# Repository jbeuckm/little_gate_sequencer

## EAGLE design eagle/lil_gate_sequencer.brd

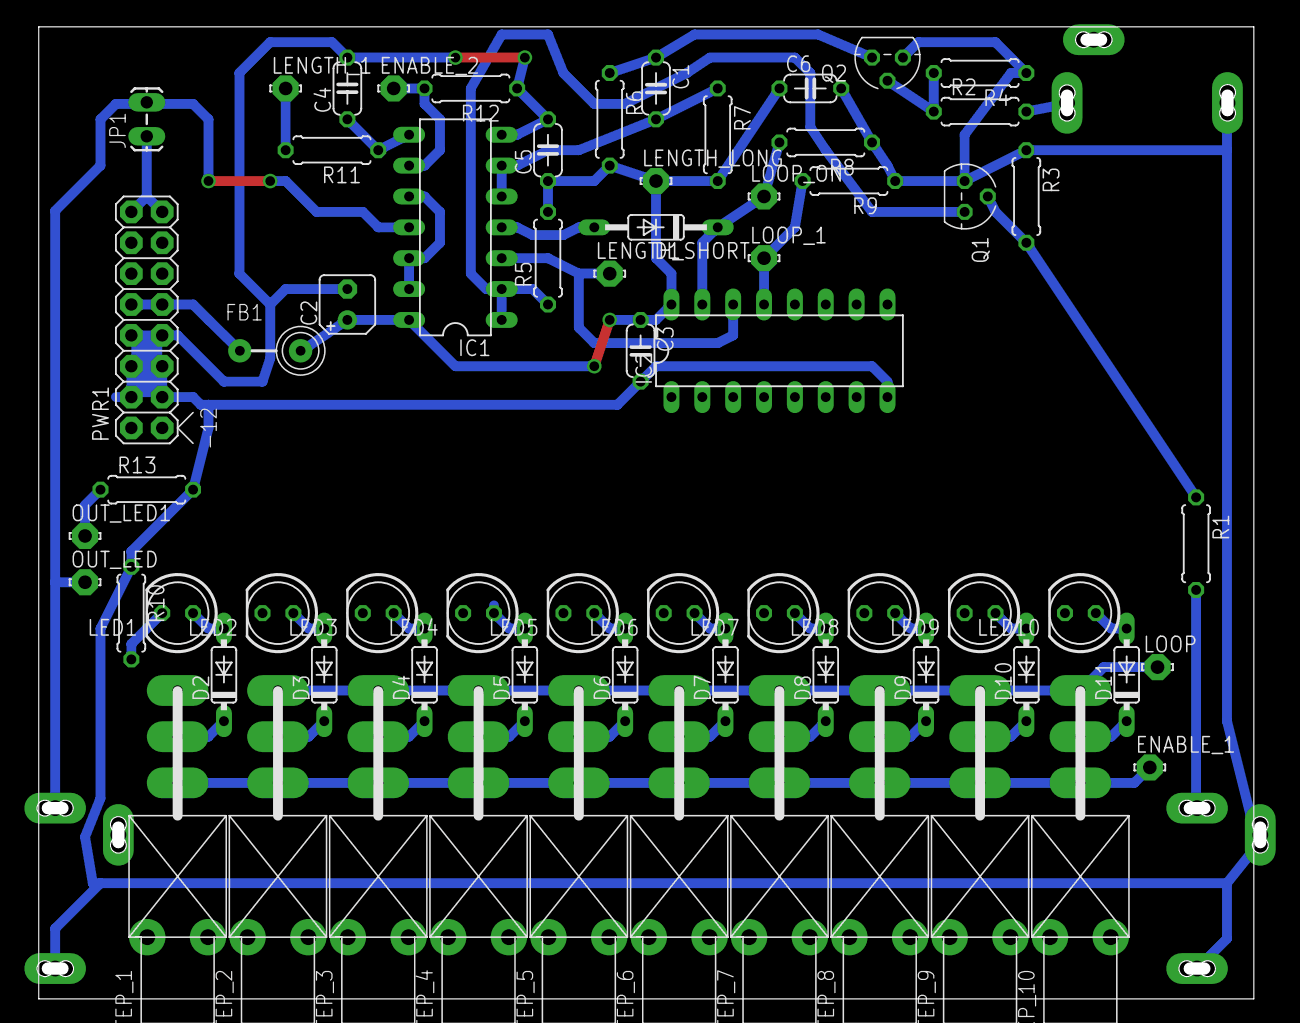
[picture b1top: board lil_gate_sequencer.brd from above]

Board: 2 copper layers, 100.0 x 79.0 mm, 70 parts (0 on the bottom side), 44 nets.

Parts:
C1, C4: 100p; C050-024X044
C2: 10u; B45181A
C3, C5, C6: 100n; C050-024X044
CLK: AUDIO-JACK; ERTHENVAR-JACK-90DEG
D1: 1N4148DO35-10; DO35-10
D2, D3, D4, D5, D6, D7, D8, D9, D10, D11: 1N4148DO35-7; DO35-7
ENABLE_1, ENABLE_2: LSP11
FB1: FB
IC1: 4093N; DIL14
IC2: 4017N; DIL16
JP1: M02LOCK_LONGPADS; 1X02_LOCK_LONGPADS
LED1, LED2, LED3, LED4, LED5, LED6, LED7, LED8, LED9, LED10: LED5MM
LENGTH_1: LSP11
LENGTH_LONG: LSP11
LENGTH_SHORT: LSP11
LOOP: LSP11
LOOP_1: LSP11
LOOP_ON: LSP11
OUT: AUDIO-JACK; ERTHENVAR-JACK-90DEG
OUT_LED, OUT_LED1: LSP11
PWR1: POWER; POWER_16
Q1, Q2: 2N3904; TO92
R1, R2, R5, R6, R7, R8, R9, R12: 10k; 0207/7
R3, R4, R10, R11, R13: 4k7; 0207/7
RST: AUDIO-JACK; ERTHENVAR-JACK-90DEG
STEP_1, STEP_2, STEP_3, STEP_4, STEP_5, STEP_6, STEP_7, STEP_8, STEP_9, STEP_10: MTS-102-C4

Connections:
+12V: C2.+, C3.1, C5.1, C6.1, FB1.P$2, IC1.14, IC2.16, LENGTH_LONG.MP, R5.2, R6.2, R7.2
GND: C2.-, C3.2, C4.2, C5.2, C6.2, CLK.P$1, CLK.P$2, IC1.7, IC2.8, OUT.P$1, PWR1.3, PWR1.4, PWR1.5, PWR1.6, PWR1.7, PWR1.8, Q1.3, Q2.3, R3.1, R4.1, R8.1, R9.1, R10.1, R12.1, R13.2, RST.P$1
unnamed: FB1.P$1, PWR1.9, PWR1.10
unnamed: Q2.2, R2.1, R4.2
unnamed: D1.A, IC1.4
unnamed: Q1.2, R1.1, R3.2
unnamed: IC1.1, IC1.2, Q1.1, R5.1
unnamed: IC1.11, JP1.2, OUT.P$3, OUT_LED.MP
unnamed: CLK.P$3, R1.2
unnamed: R2.2, RST.P$3
unnamed: D1.C, IC2.15, LOOP_ON.MP, R8.2
unnamed: C1.2, IC1.5, IC1.6, R7.1
unnamed: C1.1, Q2.1, R6.1
unnamed: IC1.3, IC2.14, LENGTH_SHORT.MP
unnamed: D2.C, STEP_1.P$2
unnamed: IC2.13, LOOP_1.MP, R9.2
unnamed: D2.A, IC2.3, LED1.A
unnamed: D3.C, STEP_2.P$2
unnamed: D3.A, IC2.2, LED2.A
unnamed: D4.C, STEP_3.P$2
unnamed: D4.A, IC2.4, LED3.A
unnamed: D5.C, STEP_4.P$2
unnamed: D5.A, IC2.7, LED4.A
unnamed: D6.C, STEP_5.P$2
unnamed: D6.A, IC2.10, LED5.A
unnamed: D7.C, STEP_6.P$2
unnamed: D7.A, IC2.1, LED6.A
unnamed: D8.C, STEP_7.P$2
unnamed: D8.A, IC2.5, LED7.A
unnamed: D9.C, STEP_8.P$2
unnamed: D9.A, IC2.6, LED8.A
unnamed: D10.C, STEP_9.P$2
unnamed: D10.A, IC2.9, LED9.A
unnamed: D11.C, STEP_10.P$2
unnamed: D11.A, IC2.11, LED10.A
unnamed: LOOP.MP, STEP_2.P$3, STEP_3.P$3, STEP_4.P$3, STEP_5.P$3, STEP_6.P$3, STEP_7.P$3, STEP_8.P$3, STEP_9.P$3, STEP_10.P$3
unnamed: LED1.K, LED2.K, LED3.K, LED4.K, LED5.K, LED6.K, LED7.K, LED8.K, LED9.K, LED10.K, R10.2
unnamed: ENABLE_1.MP, STEP_1.P$1, STEP_2.P$1, STEP_3.P$1, STEP_4.P$1, STEP_5.P$1, STEP_6.P$1, STEP_7.P$1, STEP_8.P$1, STEP_9.P$1, STEP_10.P$1
unnamed: LENGTH_1.MP, R11.2
unnamed: ENABLE_2.MP, IC1.9, R12.2
unnamed: JP1.1, PWR1.15, PWR1.16
unnamed: C4.1, IC1.8, R11.1
unnamed: IC1.10, IC1.12, IC1.13
unnamed: OUT_LED1.MP, R13.1

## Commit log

2016-01-14 schemo
2016-01-14 renumbered parts
2016-01-15 jameco toggle part
2016-01-15 layout begins
2016-01-15 routed the 4017
2016-01-15 switch and diode routes
2016-01-16 4017 routed and adjusted
2016-01-16 more routes
2016-01-17 routed
2016-01-17 reversed
2016-01-17 better routes and gcode
2016-01-17 gcode
2016-02-02 normalled gate to reset and added reset to panel
2016-02-02 panel gcode updated with reset

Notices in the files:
parts and their libraries:
SparkFun-Connectors: Licensing: Creative Commons ShareAlike 4.0 International - https://creativecommons.org/licenses/by-sa/4.0
